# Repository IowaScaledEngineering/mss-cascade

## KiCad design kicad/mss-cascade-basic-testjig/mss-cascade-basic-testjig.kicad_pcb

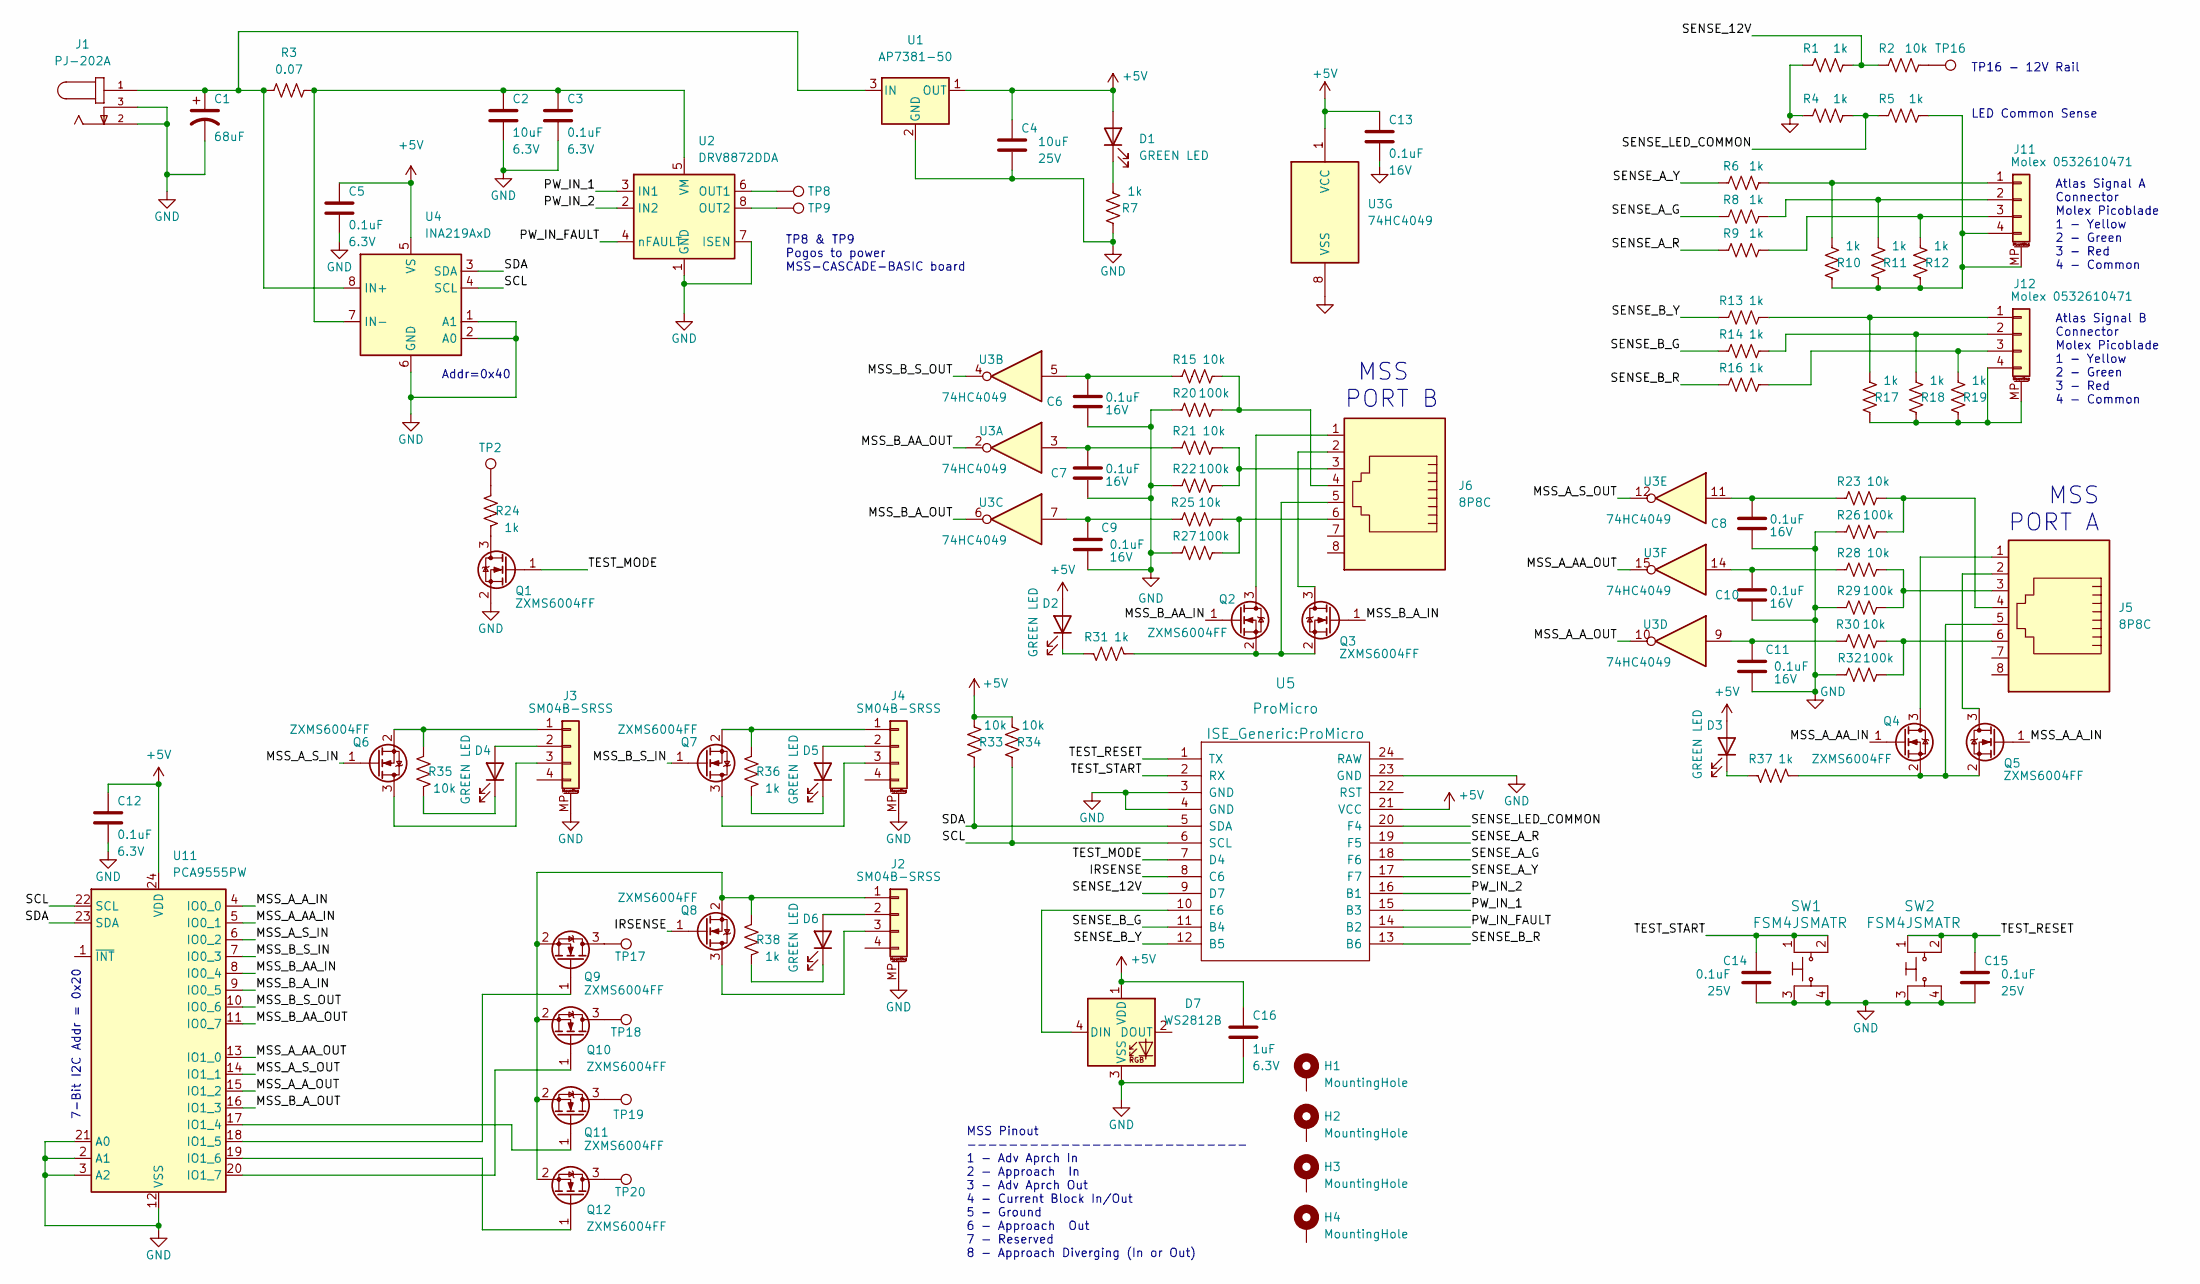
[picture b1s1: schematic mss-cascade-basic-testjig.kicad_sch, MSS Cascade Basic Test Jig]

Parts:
C1: 68uF; CP_Elec_6.3x5.8
C2: 10uF; C_0805_2012Metric; Voltage 6.3V
C3, C5, C12: 0.1uF; C_0805_2012Metric; Voltage 6.3V
C4: 10uF; C_0805_2012Metric; Voltage 25V
C6, C7, C8, C9, C10, C11, C13: 0.1uF; C_0805_2012Metric; Voltage 16V
C14, C15: 0.1uF; C_0805_2012Metric; Voltage 25V
C16: 1uF; C_0805_2012Metric; Voltage 6.3V
D1, D2, D3, D4, D5, D6: GREEN LED; LED_0805_2012Metric
D7: WS2812B; LED_WS2812B_PLCC4_5.0x5.0mm_P3.2mm
H1, H2, H3, H4: MountingHole; MountingHole_3.2mm_M3_Pad
J1: PJ-202A; CUI_PJ-202A
J2, J3, J4: SM04B-SRSS; JST_SH_SM04B-SRSS-TB_1x04-1MP_P1.00mm_Horizontal
J5, J6: 8P8C; RJ45_Amphenol_54602-x08_Horizontal
J11, J12: Molex 0532610471; Molex_PicoBlade_53261-0471_1x04-1MP_P1.25mm_Horizontal
Q1, Q2, Q3, Q4, Q5, Q6, Q7, Q8, Q9, Q10, Q11, Q12: ZXMS6004FF; SOT-23
R1, R4, R5, R6, R7, R8, R9, R10, R11, R12, R13, R14, R16, R17, R18, R19, R24, R31, R36, R37, R38: 1k; R_0805_2012Metric
R2, R15, R21, R23, R25, R28, R30, R33, R34, R35: 10k; R_0805_2012Metric
R3: 0.07; R_2512_6332Metric
R20, R22, R26, R27, R29, R32: 100k; R_0805_2012Metric
SW1, SW2: FSM4JSMATR; TE_FSM4JSMA; MPN FSM4JSMATR; Digi-Key_PN 450-1759-1-ND
TP2, TP8, TP9, TP16, TP17, TP18, TP19, TP20: TestPoint; PinHeader_1x01_P2.54mm_Vertical
U1: AP7381-50; SOT-89-3
U2: DRV8872DDA; Texas_HSOP-8-1EP_3.9x4.9mm_P1.27mm
U3: 74HC4049; SO-16_3.9x9.9mm_P1.27mm
U4: INA219AxD; SOIC-8_3.9x4.9mm_P1.27mm
U5: ProMicro
U11: PCA9555PW; TSSOP-24_4.4x7.8mm_P0.65mm

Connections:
+5V: C4.1, C5.1, C12.1, C13.1, C16.1, D1.2 (A), D2.2 (A), D3.2 (A), D7.1 (VDD), R33.1, R34.1, U1.1 (OUT), U3.1 (VCC), U4.5 (VS), U5.21 (VCC), U11.24 (VDD)
/IRSENSE: Q8.1 (G), U5.8 (C6)
/MSS_A_AA_IN: Q4.1 (G), U11.5 (IO0_1)
/MSS_A_AA_OUT: U3.15, U11.13 (IO1_0)
/MSS_A_A_IN: Q5.1 (G), U11.4 (IO0_0)
/MSS_A_A_OUT: U3.10, U11.15 (IO1_2)
/MSS_A_S_IN: Q6.1 (G), U11.6 (IO0_2)
/MSS_A_S_OUT: U3.12, U11.14 (IO1_1)
/MSS_B_AA_IN: Q2.1 (G), U11.8 (IO0_4)
/MSS_B_AA_OUT: U3.2, U11.11 (IO0_7)
/MSS_B_A_IN: Q3.1 (G), U11.9 (IO0_5)
/MSS_B_A_OUT: U3.6, U11.16 (IO1_3)
/MSS_B_S_IN: Q7.1 (G), U11.7 (IO0_3)
/MSS_B_S_OUT: U3.4, U11.10 (IO0_6)
/PW_IN_1: U2.3 (IN1), U5.15 (B3)
/PW_IN_2: U2.2 (IN2), U5.16 (B1)
/PW_IN_FAULT: U2.4 (nFAULT), U5.14 (B2)
/SCL: R34.2, U4.4 (SCL), U5.6 (SCL), U11.22 (SCL)
/SDA: R33.2, U4.3 (SDA), U5.5 (SDA), U11.23 (SDA)
/SENSE_12V: R1.2, R2.1, U5.9 (D7)
/SENSE_A_G: R8.1, U5.18 (F6)
/SENSE_A_R: R9.1, U5.19 (F5)
/SENSE_A_Y: R6.1, U5.17 (F7)
/SENSE_B_G: R14.1, U5.11 (B4)
/SENSE_B_R: R16.1, U5.13 (B6)
/SENSE_B_Y: R13.1, U5.12 (B5)
/SENSE_LED_COMMON: R4.2, R5.1, U5.20 (F4)
/TEST_MODE: Q1.1 (G), U5.7 (D4)
/TEST_RESET: C15.1, SW2.1, SW2.2, U5.1 (TX)
/TEST_START: C14.1, SW1.1, SW1.2, U5.2 (RX)
GND: C1.2, C2.2, C3.2, C4.2, C5.2, C6.2, C7.2, C8.2, C9.2, C10.2, C11.2, C12.2, C13.2, C14.2, C15.2, C16.2, D7.3 (VSS), J1.2, J1.3, J2.MP (MountPin), J3.MP (MountPin), J4.MP (MountPin), Q1.2 (S), R1.1, R4.1, R7.2, R20.2, R22.2, R26.2, R27.2, R29.2, R32.2, SW1.3, SW1.4, SW2.3, SW2.4, U1.2 (GND), U2.1 (GND), U2.7 (ISEN), U2.9 (GND), U3.8 (VSS), U4.1 (A1), U4.2 (A0), U4.6 (GND), U5.3 (GND), U5.4 (GND), U5.23 (GND), U11.2 (A1), U11.3 (A2), U11.12 (VSS), U11.21 (A0)
unnamed: C1.1, J1.1, R3.2, U1.3 (IN), U4.8 (IN+)
unnamed: C2.1, C3.1, R3.1, U2.5 (VM), U4.7 (IN-)
unnamed: C6.1, R15.2, U3.5
unnamed: C7.1, R21.2, U3.3
unnamed: C8.1, R23.2, U3.11
unnamed: C9.1, R25.2, U3.7
unnamed: C10.1, R28.2, U3.14
unnamed: C11.1, R30.2, U3.9
unnamed: D1.1 (K), R7.1
unnamed: D2.1 (K), R31.2
unnamed: D3.1 (K), R37.2
unnamed: D4.1 (K), R35.1
unnamed: D4.2 (A), J3.2
unnamed: D5.1 (K), R36.1
unnamed: D5.2 (A), J4.2
unnamed: D6.1 (K), R38.1
unnamed: D6.2 (A), J2.2
unnamed: D7.4 (DIN), U5.10 (E6)
unnamed: J2.1, Q8.2 (S), Q9.2 (S), Q10.2 (S), Q11.2 (S), Q12.2 (S), R38.2
unnamed: J2.3, Q8.3 (D)
unnamed: J3.1, Q6.2 (S), R35.2
unnamed: J3.3, Q6.3 (D)
unnamed: J4.1, Q7.2 (S), R36.2
unnamed: J4.3, Q7.3 (D)
unnamed: J5.1, Q4.3 (D)
unnamed: J5.2, Q5.3 (D)
unnamed: J5.3, R28.1, R29.1
unnamed: J5.4, R23.1, R26.1
unnamed: J5.5, Q4.2 (S), Q5.2 (S), R37.1
unnamed: J5.6, R30.1, R32.1
unnamed: J6.1, Q2.3 (D)
unnamed: J6.2, Q3.3 (D)
unnamed: J6.3, R21.1, R22.1
unnamed: J6.4, R15.1, R20.1
unnamed: J6.5, Q2.2 (S), Q3.2 (S), R31.1
unnamed: J6.6, R25.1, R27.1
unnamed: J11.1, R6.2, R10.1
unnamed: J11.2, R8.2, R11.1
unnamed: J11.3, R9.2, R12.1
unnamed: J11.4, J11.MP (MountPin), R5.2, R10.2, R11.2, R12.2
unnamed: J12.1, R13.2, R17.1
unnamed: J12.2, R14.2, R18.1
unnamed: J12.3, R16.2, R19.1
unnamed: J12.4, J12.MP (MountPin), R17.2, R18.2, R19.2
unnamed: Q1.3 (D), R24.1
unnamed: Q9.1 (G), U11.18 (IO1_5)
unnamed: Q9.3 (D), TP17.1
unnamed: Q10.1 (G), U11.20 (IO1_7)
unnamed: Q10.3 (D), TP18.1
unnamed: Q11.1 (G), U11.17 (IO1_4)
unnamed: Q11.3 (D), TP19.1
unnamed: Q12.1 (G), U11.19 (IO1_6)
unnamed: Q12.3 (D), TP20.1
unnamed: R2.2, TP16.1
unnamed: R24.2, TP2.1
unnamed: TP8.1, U2.6 (OUT1)
unnamed: TP9.1, U2.8 (OUT2)

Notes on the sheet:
MSS PORT A
Addr=0x40
Atlas Signal B Connector Molex Picoblade 1 - Yellow 2 - Green 3 - Red 4 - Common
MSS PORT B
MSS Pinout --------------------------- 1 - Adv Aprch In 2 - Approach In 3 - Adv Aprch Out 4 - Current Block In/Out 5 - Ground 6 - Approach Out 7 - Reserved 8 - Approach Diverging (In or Out)
TP8 & TP9 Pogos to power MSS-CASCADE-BASIC board
Atlas Signal A Connector Molex Picoblade 1 - Yellow 2 - Green 3 - Red 4 - Common
TP16 - 12V Rail
LED Common Sense
7-Bit I2C Addr = 0x20

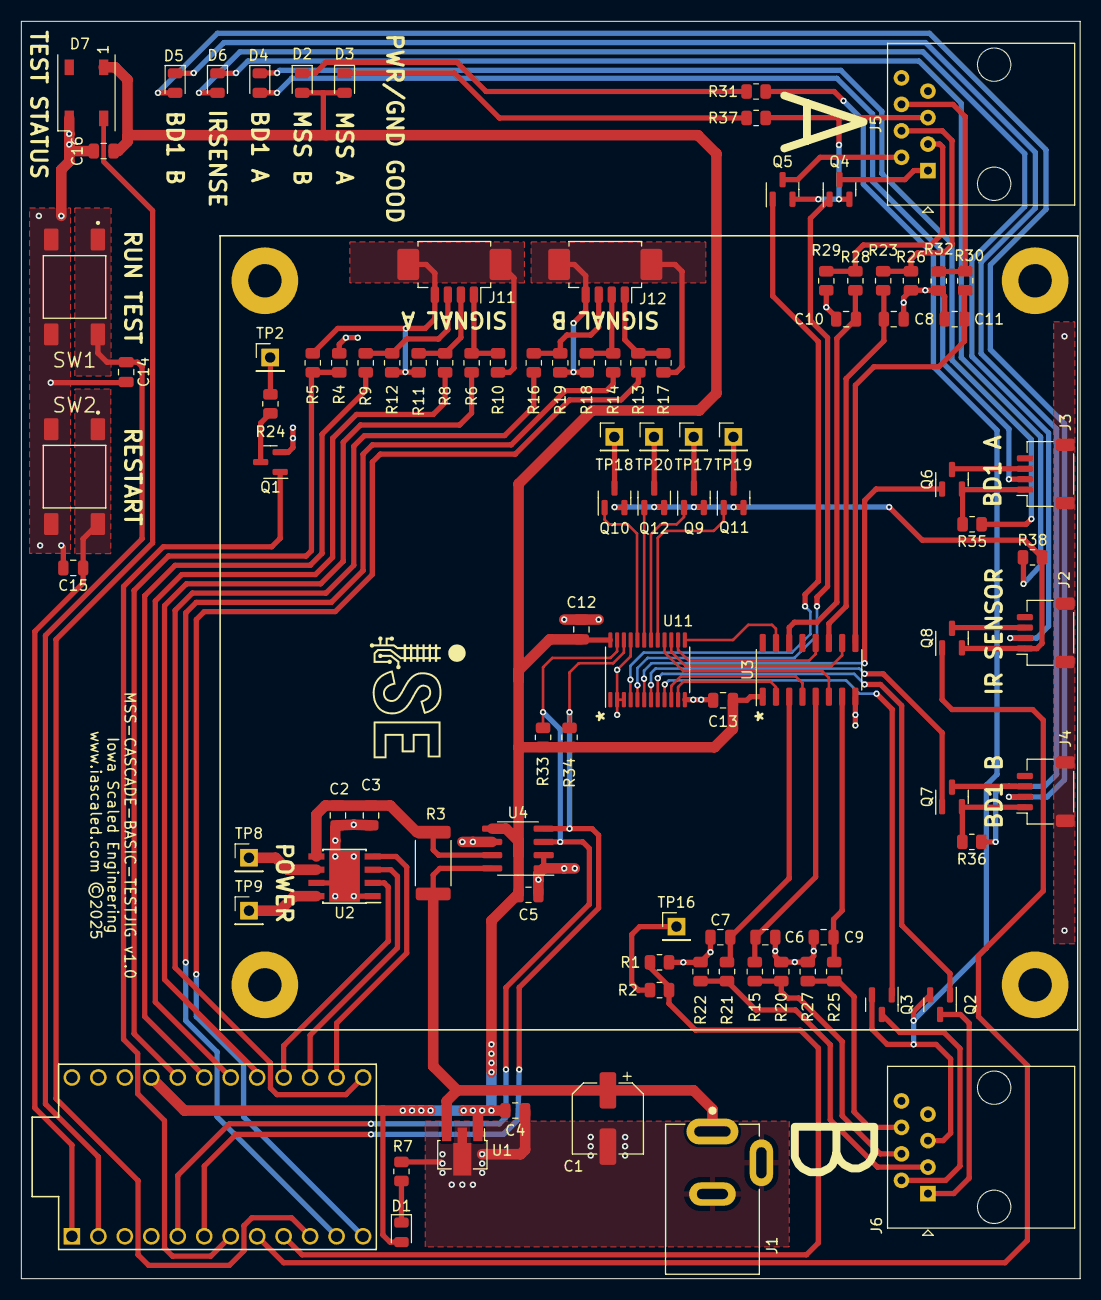
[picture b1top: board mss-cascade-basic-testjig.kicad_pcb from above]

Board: 2 copper layers, 101.6 x 120.7 mm, 101 parts (0 on the bottom side), 88 nets.

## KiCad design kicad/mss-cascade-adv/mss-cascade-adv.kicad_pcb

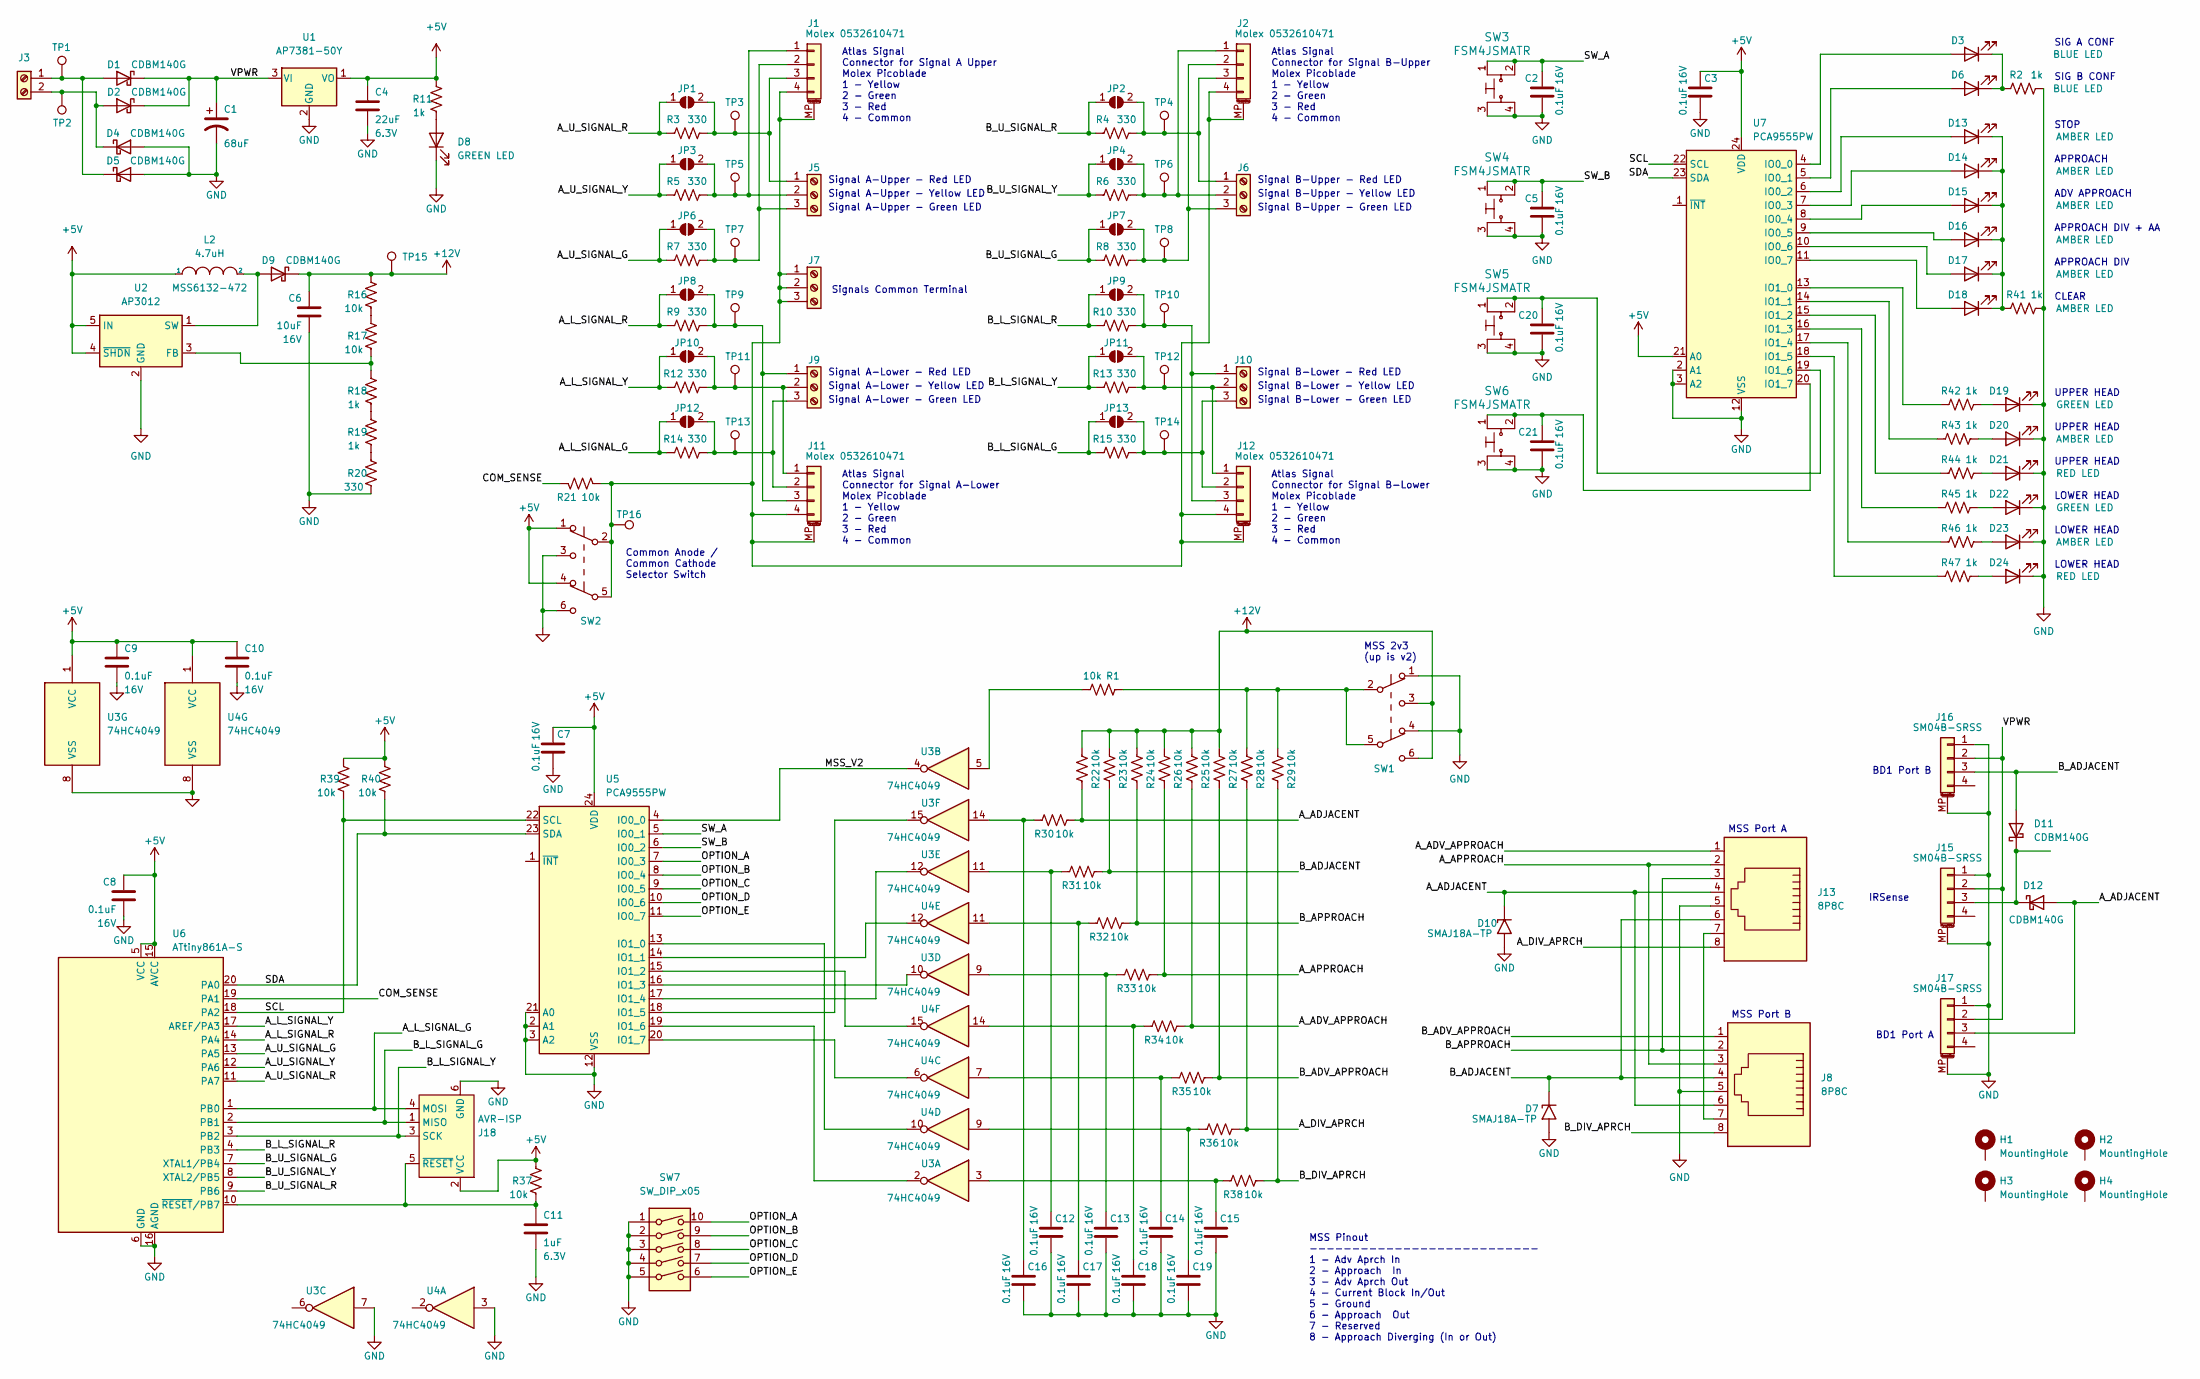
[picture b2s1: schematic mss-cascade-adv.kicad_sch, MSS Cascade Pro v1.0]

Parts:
C1: 68uF; CP_Elec_6.3x5.8
C2, C3, C5, C7, C8, C9, C10, C12, C13, C14, C15, C16, C17, C18, C19, C20, C21: 0.1uF; C_0805_2012Metric; Voltage 16V
C4: 22uF; C_0805_2012Metric; Voltage 6.3V
C6: 10uF; C_0805_2012Metric; Voltage 16V
C11: 1uF; C_0805_2012Metric; Voltage 6.3V
D1, D2, D4, D5, D9, D11, D12: CDBM140G; SOD-123T
D3, D6: BLUE LED; LED_0805_2012Metric
D7, D10: SMAJ18A-TP; D_SMA
D8, D19, D22: GREEN LED; LED_0805_2012Metric
D13, D14, D15, D16, D17, D18, D20, D23: AMBER LED; LED_0805_2012Metric
D21, D24: RED LED; LED_0805_2012Metric
H1, H2, H3, H4: MountingHole; MountingHole_3.2mm_M3_Pad
J1, J2, J11, J12: Molex 0532610471; Molex_PicoBlade_53261-0471_1x04-1MP_P1.25mm_Horizontal
J3: Screw_Terminal_01x02; TerminalBlock_RND_205-00012_1x02_P5.00mm_Horizontal
J5, J6, J7, J9, J10: Screw_Terminal_01x02; TerminalBlock_MetzConnect_Type059_RT06303HBWC_1x03_P3.50mm_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
J8, J13: 8P8C; RJ45_Amphenol_54602-x08_Horizontal
J15, J16, J17: SM04B-SRSS; JST_SH_SM04B-SRSS-TB_1x04-1MP_P1.00mm_Horizontal
J18: AVR-ISP; Tag-Connect_TC2030-IDC-NL_2x03_P1.27mm_Vertical
JP1, JP2, JP3, JP4, JP6, JP7, JP8, JP9, JP10, JP11, JP12, JP13: SolderJumper_2_Open; SolderJumper-2_P1.3mm_Open_RoundedPad1.0x1.5mm
L2: 4.7uH; MSS6132-xxxMLC
R1, R16, R17, R21, R22, R23, R24, R25, R26, R27, R28, R29, R30, R31, R32, R33, R34, R35, R36, R37, R38, R39, R40: 10k; R_0805_2012Metric
R2, R11, R18, R19, R41, R42, R43, R44, R45, R46, R47: 1k; R_0805_2012Metric
R3, R4, R5, R6, R7, R8, R9, R10, R12, R13, R14, R15, R20: 330; R_0805_2012Metric
SW1, SW2: JS202011SCQN; SW_JS202011SCQN
SW3, SW4, SW5, SW6: FSM4JSMATR; TE_FSM4JSMA; MPN FSM4JSMATR; Digi-Key_PN 450-1759-1-ND
SW7: SW_DIP_x05; SW_DIP_SPSTx05_Slide_6.7x14.26mm_W8.61mm_P2.54mm_LowProfile
TP1, TP2, TP3, TP4, TP5, TP6, TP7, TP8, TP9, TP10, TP11, TP12, TP13, TP14, TP15, TP16: TestPoint; TestPoint_Pad_D2.0mm
U1: AP7381-50Y; SOT-89-3
U2: AP3012; SOT-23-5
U3, U4: 74HC4049; SO-16_3.9x9.9mm_P1.27mm
U5, U7: PCA9555PW; TSSOP-24_4.4x7.8mm_P0.65mm
U6: ATtiny861A-S; SOIC-20W_7.5x12.8mm_P1.27mm

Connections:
+5V: C3.1, C4.1, C7.1, C8.1, C9.1, C10.1, J18.2 (VCC), L2.1, R11.2, R37.2, R39.2, R40.2, SW2.1 (A), SW2.4 (A), U1.1 (VO), U2.4 (~SHDN), U2.5 (IN), U3.1 (VCC), U4.1 (VCC), U5.24 (VDD), U6.5 (VCC), U6.15 (AVCC), U7.21 (A0), U7.24 (VDD)
+12V: C6.1, D9.1 (K), R16.2, R22.1, R23.1, R24.1, R25.1, R26.2, R27.1, SW1.3 (C), SW1.6 (C), TP15.1
/A_ADJACENT: D10.1 (A1), D12.2 (A), J8.6, J13.4, J17.3, R22.2, R30.1
/A_ADV_APPROACH: J13.1, R25.2, R34.1
/A_APPROACH: J8.3, J13.2, R26.1, R33.1
/A_DIV_APRCH: J13.8, R28.2, R36.1
/A_L_SIGNAL_G: J18.4 (MOSI), JP12.1 (A), R14.1, U6.1 (PB0)
/A_L_SIGNAL_R: JP8.1 (A), R9.1, U6.14 (PA4)
/A_L_SIGNAL_Y: JP10.1 (A), R12.1, U6.17 (AREF/PA3)
/A_U_SIGNAL_G: JP6.1 (A), R7.1, U6.13 (PA5)
/A_U_SIGNAL_R: JP1.1 (A), R3.1, U6.11 (PA7)
/A_U_SIGNAL_Y: JP3.1 (A), R5.1, U6.12 (PA6)
/B_ADJACENT: D7.1 (A1), D11.2 (A), J8.4, J13.6, J16.3, R23.2, R31.1
/B_ADV_APPROACH: J8.1, R27.2, R35.1
/B_APPROACH: J8.2, J13.3, R24.2, R32.1
/B_DIV_APRCH: J8.8, R29.2, R38.1
/B_L_SIGNAL_G: J18.1 (MISO), JP13.1 (A), R15.1, U6.2 (PB1)
/B_L_SIGNAL_R: JP9.1 (A), R10.1, U6.4 (PB3)
/B_L_SIGNAL_Y: J18.3 (SCK), JP11.1 (A), R13.1, U6.3 (PB2)
/B_U_SIGNAL_G: JP7.1 (A), R8.1, U6.7 (XTAL1/PB4)
/B_U_SIGNAL_R: JP2.1 (A), R4.1, U6.9 (PB6)
/B_U_SIGNAL_Y: JP4.1 (A), R6.1, U6.8 (XTAL2/PB5)
/COM_SENSE: R21.1, U6.19 (PA1)
/MSS_V2: U3.4, U5.4 (IO0_0)
/OPTION_A: SW7.10, U5.7 (IO0_3)
/OPTION_B: SW7.9, U5.8 (IO0_4)
/OPTION_C: SW7.8, U5.9 (IO0_5)
/OPTION_D: SW7.7, U5.10 (IO0_6)
/OPTION_E: SW7.6, U5.11 (IO0_7)
/SCL: R39.1, U5.22 (SCL), U6.18 (PA2), U7.22 (SCL)
/SDA: R40.1, U5.23 (SDA), U6.20 (PA0), U7.23 (SDA)
/SW_A: C2.1, SW3.1, SW3.2, U5.5 (IO0_1)
/SW_B: C5.1, SW4.1, SW4.2, U5.6 (IO0_2)
/VPWR: C1.1, D1.1 (K), D2.1 (K), J15.2, J16.2, J17.2, U1.3 (VI)
GND: C1.2, C2.2, C3.2, C4.2, C5.2, C6.2, C7.2, C8.2, C9.2, C10.2, C11.2, C12.2, C13.2, C14.2, C15.2, C16.2, C17.2, C18.2, C19.2, C20.2, C21.2, D4.2 (A), D5.2 (A), D7.2 (A2), D8.1 (K), D10.2 (A2), D19.1 (K), D20.1 (K), D21.1 (K), D22.1 (K), D23.1 (K), D24.1 (K), J8.5, J13.5, J15.1, J15.MP (MountPin), J16.1, J16.MP (MountPin), J17.1, J17.MP (MountPin), J18.6 (GND), R2.2, R20.1, R41.2, SW1.1 (A), SW1.4 (A), SW2.3 (C), SW2.6 (C), SW3.3, SW3.4, SW4.3, SW4.4, SW5.3, SW5.4, SW6.3, SW6.4, SW7.1, SW7.2, SW7.3, SW7.4, SW7.5, U1.2 (GND), U2.2 (GND), U3.7, U3.8 (VSS), U4.3, U4.8 (VSS), U5.2 (A1), U5.3 (A2), U5.12 (VSS), U5.21 (A0), U6.6 (GND), U6.16 (AGND), U7.2 (A1), U7.3 (A2), U7.12 (VSS)
unnamed: C11.1, J18.5 (~RESET), R37.1, U6.10 (~RESET/PB7)
unnamed: C12.1, R31.2, U3.11
unnamed: C13.1, R33.2, U3.9
unnamed: C14.1, R35.2, U4.7
unnamed: C15.1, R38.2, U3.3
unnamed: C16.1, R30.2, U3.14
unnamed: C17.1, R32.2, U4.11
unnamed: C18.1, R34.2, U4.14
unnamed: C19.1, R36.2, U4.9
unnamed: C20.1, SW5.1, SW5.2, U7.19 (IO1_6)
unnamed: C21.1, SW6.1, SW6.2, U7.20 (IO1_7)
unnamed: D1.2 (A), D5.1 (K), J3.1, TP1.1
unnamed: D2.2 (A), D4.1 (K), J3.2, TP2.1
unnamed: D3.1 (K), D6.1 (K), R2.1
unnamed: D3.2 (A), U7.4 (IO0_0)
unnamed: D6.2 (A), U7.5 (IO0_1)
unnamed: D8.2 (A), R11.1
unnamed: D9.2 (A), L2.2, U2.1 (SW)
unnamed: D11.1 (K), D12.1 (K), J15.3
unnamed: D13.1 (K), D14.1 (K), D15.1 (K), D16.1 (K), D17.1 (K), D18.1 (K), R41.1
unnamed: D13.2 (A), U7.6 (IO0_2)
unnamed: D14.2 (A), U7.7 (IO0_3)
unnamed: D15.2 (A), U7.8 (IO0_4)
unnamed: D16.2 (A), U7.9 (IO0_5)
unnamed: D17.2 (A), U7.10 (IO0_6)
unnamed: D18.2 (A), U7.11 (IO0_7)
unnamed: D19.2 (A), R42.2
unnamed: D20.2 (A), R43.2
unnamed: D21.2 (A), R44.2
unnamed: D22.2 (A), R45.2
unnamed: D23.2 (A), R46.2
unnamed: D24.2 (A), R47.2
unnamed: J1.1, J5.2, JP3.2 (B), R5.2, TP5.1
unnamed: J1.2, J5.3, JP6.2 (B), R7.2, TP7.1
unnamed: J1.3, J5.1, JP1.2 (B), R3.2, TP3.1
unnamed: J1.4, J1.MP (MountPin), J2.4, J2.MP (MountPin), J7.1, J7.2, J7.3, J11.4, J11.MP (MountPin), J12.4, J12.MP (MountPin), R21.2, SW2.2 (B), SW2.5 (B), TP16.1
unnamed: J2.1, J6.2, JP4.2 (B), R6.2, TP6.1
unnamed: J2.2, J6.3, JP7.2 (B), R8.2, TP8.1
unnamed: J2.3, J6.1, JP2.2 (B), R4.2, TP4.1
unnamed: J10.1, J12.3, JP9.2 (B), R10.2, TP10.1
unnamed: J10.2, J12.1, JP11.2 (B), R13.2, TP12.1
unnamed: J10.3, J12.2, JP13.2 (B), R15.2, TP14.1
unnamed: J9.2, J11.1, JP10.2 (B), R12.2, TP11.1
unnamed: J9.3, J11.2, JP12.2 (B), R14.2, TP13.1
unnamed: J9.1, J11.3, JP8.2 (B), R9.2, TP9.1
unnamed: J8.7, J13.7
unnamed: R1.1, U3.5
unnamed: R1.2, R28.1, R29.1, SW1.2 (B), SW1.5 (B)
unnamed: R16.1, R17.2
unnamed: R17.1, R18.2, U2.3 (FB)
unnamed: R18.1, R19.2
unnamed: R19.1, R20.2
unnamed: R42.1, U7.13 (IO1_0)
unnamed: R43.1, U7.14 (IO1_1)
unnamed: R44.1, U7.15 (IO1_2)
unnamed: R45.1, U7.16 (IO1_3)
unnamed: R46.1, U7.17 (IO1_4)
unnamed: R47.1, U7.18 (IO1_5)
unnamed: U3.2, U5.19 (IO1_6)
unnamed: U3.10, U5.16 (IO1_3)
unnamed: U3.12, U5.17 (IO1_4)
unnamed: U3.15, U5.18 (IO1_5)
unnamed: U4.6, U5.20 (IO1_7)
unnamed: U4.10, U5.13 (IO1_0)
unnamed: U4.12, U5.14 (IO1_1)
unnamed: U4.15, U5.15 (IO1_2)

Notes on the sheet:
UPPER HEAD
Signal A-Upper - Yellow LED
APPROACH
Common Anode / Common Cathode Selector Switch
Atlas Signal Connector for Signal A Upper Molex Picoblade 1 - Yellow 2 - Green 3 - Red 4 - Common
LOWER HEAD
Signal A-Lower - Green LED
MSS 2v3 (up is v2)
MSS Port A
IRSense
Signal B-Lower - Red LED
Signal A-Lower - Yellow LED
CLEAR
BD1 Port B
MSS Port B
APPROACH DIV
SIG A CONF
Atlas Signal Connector for Signal B-Upper Molex Picoblade 1 - Yellow 2 - Green 3 - Red 4 - Common
STOP
BD1 Port A
Signals Common Terminal
ADV APPROACH
SIG B CONF
Signal B-Upper - Red LED
APPROACH DIV + AA
Signal A-Lower - Red LED
Signal B-Lower - Green LED
Atlas Signal Connector for Signal B-Lower Molex Picoblade 1 - Yellow 2 - Green 3 - Red 4 - Common
Atlas Signal Connector for Signal A-Lower Molex Picoblade 1 - Yellow 2 - Green 3 - Red 4 - Common
Signal A-Upper - Green LED
Signal B-Upper - Green LED
Signal B-Lower - Yellow LED
Signal B-Upper - Yellow LED
Signal A-Upper - Red LED
MSS Pinout --------------------------- 1 - Adv Aprch In 2 - Approach In 3 - Adv Aprch Out 4 - Current Block In/Out 5 - Ground 6 - Approach Out 7 - Reserved 8 - Approach Diverging (In or Out)

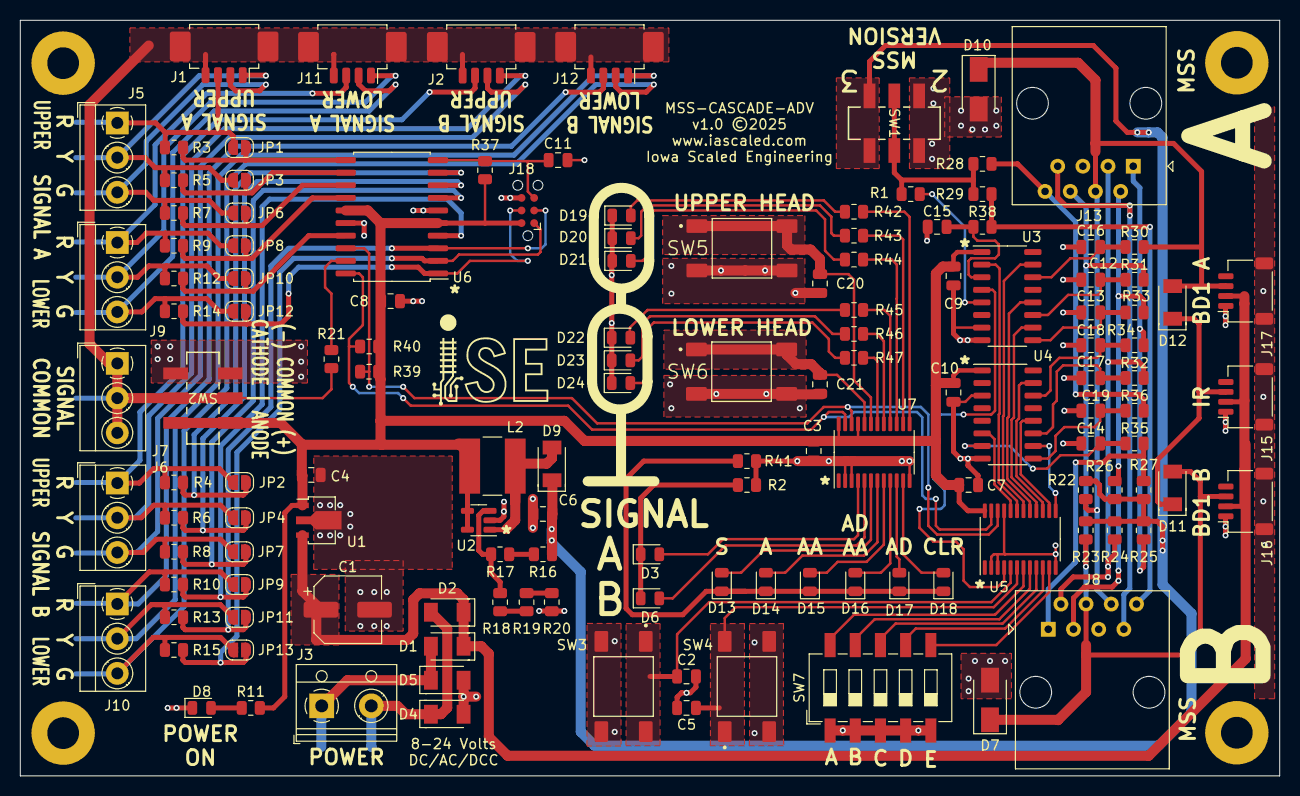
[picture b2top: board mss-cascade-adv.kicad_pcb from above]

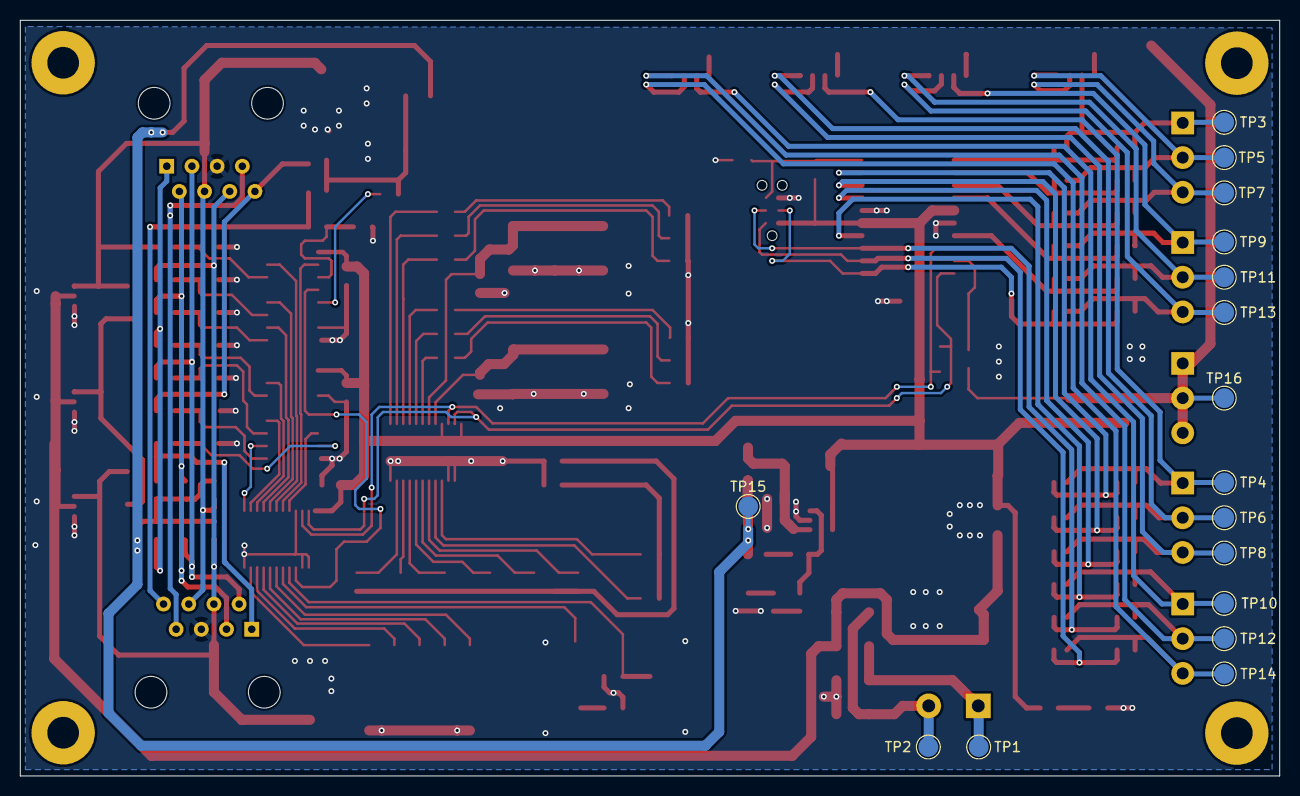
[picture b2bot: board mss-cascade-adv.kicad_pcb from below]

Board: 2 copper layers, 127.0 x 76.2 mm, 155 parts (16 on the bottom side), 101 nets.

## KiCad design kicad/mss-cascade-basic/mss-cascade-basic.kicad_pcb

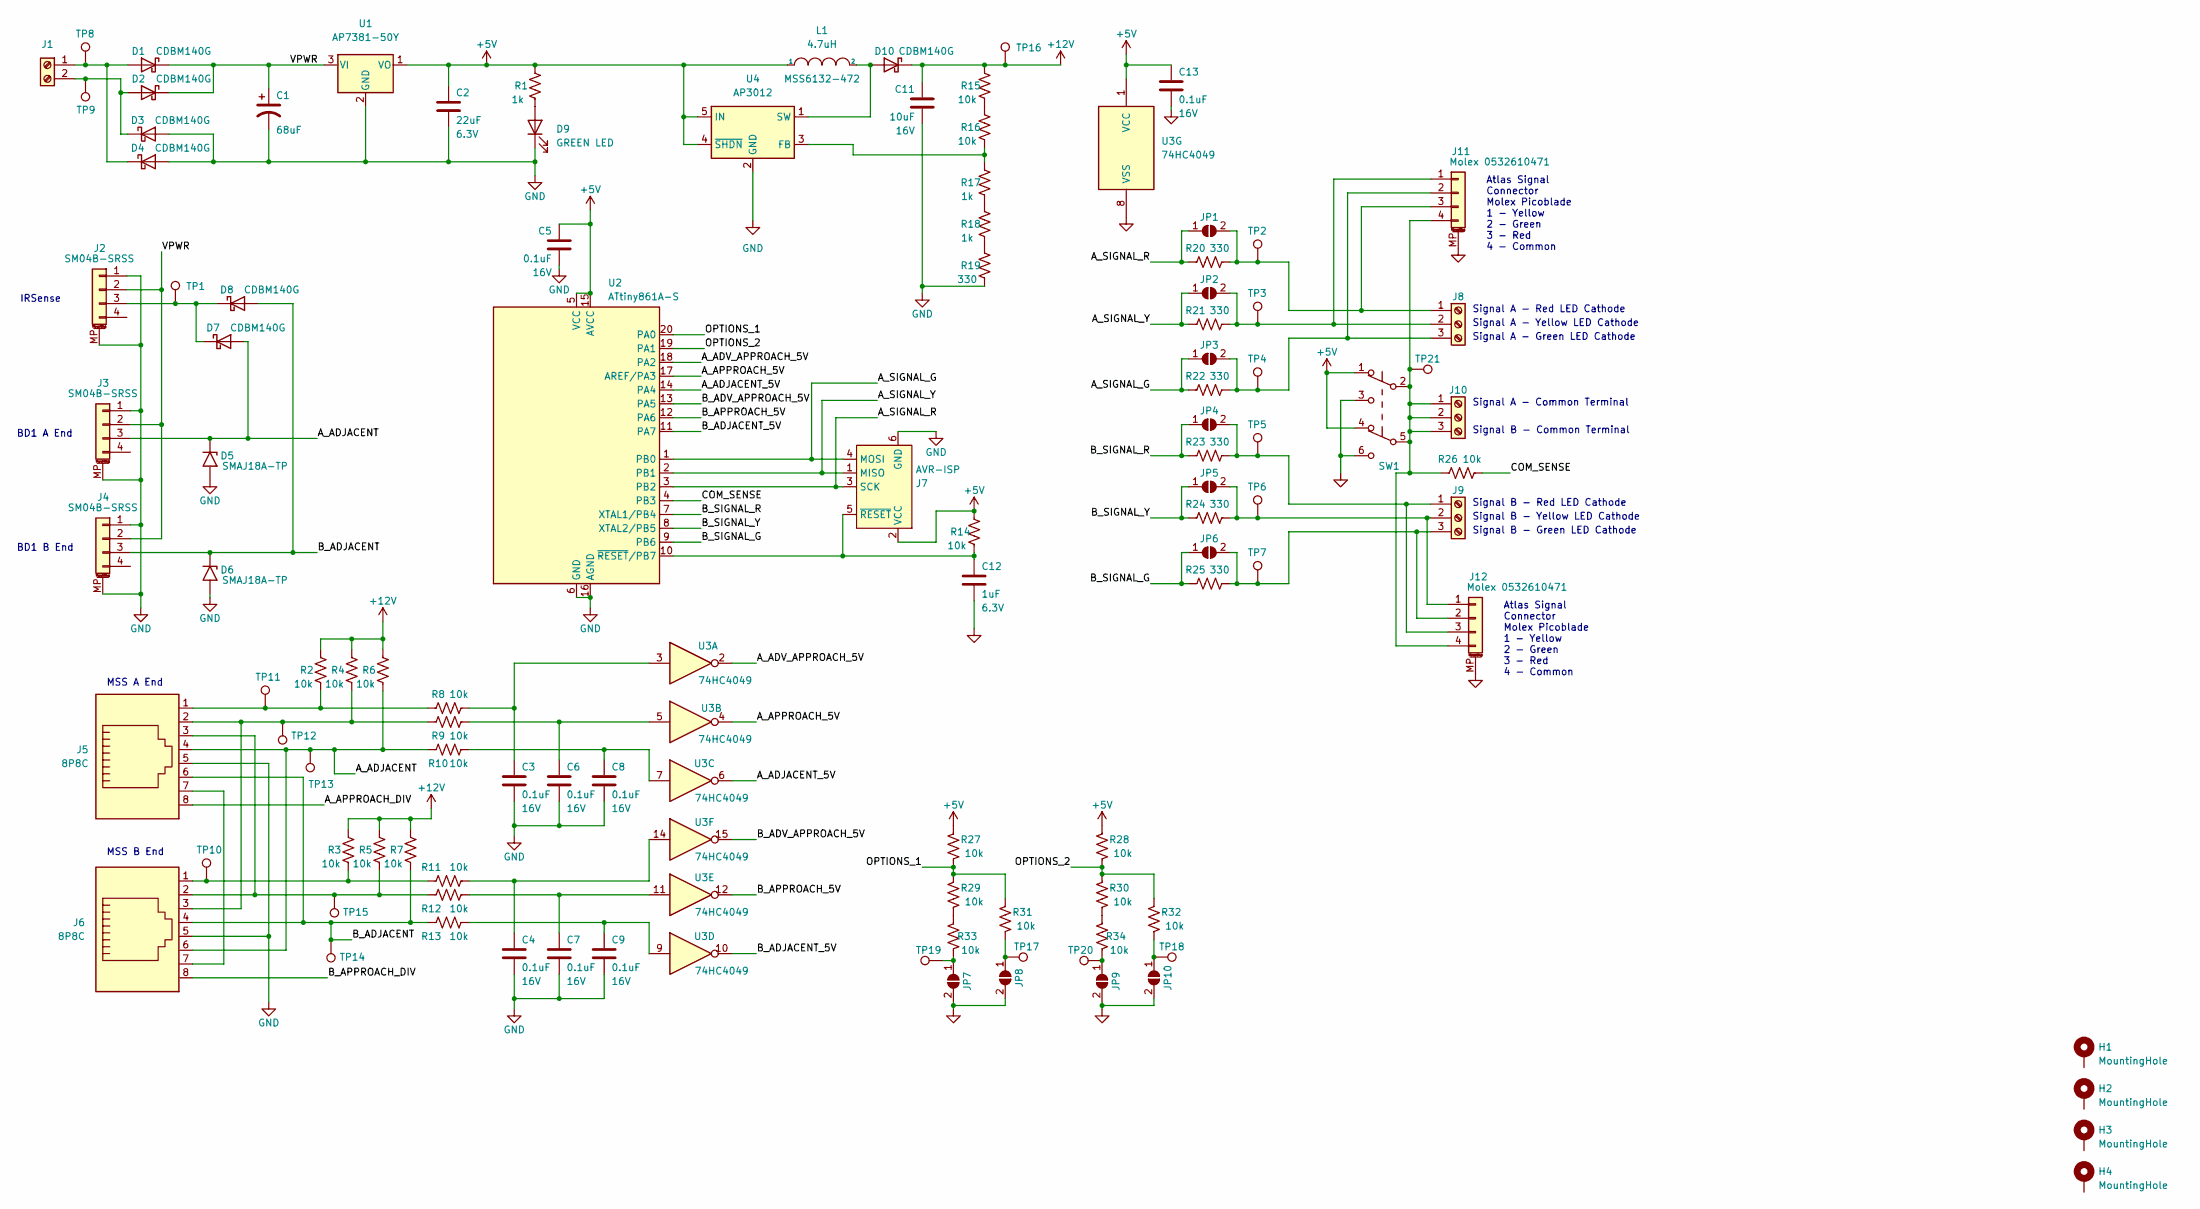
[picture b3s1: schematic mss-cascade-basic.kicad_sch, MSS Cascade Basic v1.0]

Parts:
C1: 68uF; CP_Elec_6.3x5.8
C2: 22uF; C_0805_2012Metric; Voltage 6.3V
C3, C4, C5, C6, C7, C8, C9, C13: 0.1uF; C_0805_2012Metric; Voltage 16V
C11: 10uF; C_0805_2012Metric; Voltage 16V
C12: 1uF; C_0805_2012Metric; Voltage 6.3V
D1, D2, D3, D4, D7, D8, D10: CDBM140G; SOD-123T
D5, D6: SMAJ18A-TP; D_SMA
D9: GREEN LED; LED_0805_2012Metric
H1, H2, H3, H4: MountingHole; MountingHole_3.2mm_M3_Pad
J1: Screw_Terminal_01x02; TerminalBlock_RND_205-00012_1x02_P5.00mm_Horizontal
J2, J3, J4: SM04B-SRSS; JST_SH_SM04B-SRSS-TB_1x04-1MP_P1.00mm_Horizontal
J5, J6: 8P8C; RJ45_Amphenol_54602-x08_Horizontal
J7: AVR-ISP; Tag-Connect_TC2030-IDC-NL_2x03_P1.27mm_Vertical
J8, J9, J10: Screw_Terminal_01x02; TerminalBlock_MetzConnect_Type059_RT06303HBWC_1x03_P3.50mm_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
J11, J12: Molex 0532610471; Molex_PicoBlade_53261-0471_1x04-1MP_P1.25mm_Horizontal
JP1, JP2, JP3, JP4, JP5, JP6, JP7, JP8, JP9, JP10: SolderJumper_2_Open; SolderJumper-2_P1.3mm_Open_RoundedPad1.0x1.5mm
L1: 4.7uH; MSS6132-xxxMLC
R1, R17, R18: 1k; R_0805_2012Metric
R2, R3, R4, R5, R6, R7, R8, R9, R10, R11, R12, R13, R14, R15, R16, R26, R27, R28, R29, R30, R31, R32, R33, R34: 10k; R_0805_2012Metric
R19, R20, R21, R22, R23, R24, R25: 330; R_0805_2012Metric
SW1: JS202011SCQN; SW_JS202011SCQN
TP1, TP2, TP3, TP4, TP5, TP6, TP7, TP8, TP9, TP10, TP11, TP12, TP13, TP14, TP15, TP16, TP17, TP18, TP19, TP20, TP21: TestPoint; TestPoint_Pad_D2.0mm
U1: AP7381-50Y; SOT-89-3
U2: ATtiny861A-S; SOIC-20W_7.5x12.8mm_P1.27mm
U3: 74HC4049; SO-16_3.9x9.9mm_P1.27mm
U4: AP3012; SOT-23-5

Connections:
+5V: C2.1, C5.1, C13.1, J7.2 (VCC), L1.1, R1.2, R14.2, R27.2, R28.2, SW1.1 (A), SW1.4 (A), U1.1 (VO), U2.5 (VCC), U2.15 (AVCC), U3.1 (VCC), U4.4 (~SHDN), U4.5 (IN)
+12V: C11.1, D10.1 (K), R2.2, R3.2, R4.2, R5.2, R6.2, R7.2, R15.2, TP16.1
/A_ADJACENT: D5.1 (A1), D7.2 (A), J3.3, J5.4, J6.6, R6.1, R10.2, TP13.1
/A_ADJACENT_5V: U2.14 (PA4), U3.6
/A_ADV_APPROACH_5V: U2.18 (PA2), U3.2
/A_APPROACH_5V: U2.17 (AREF/PA3), U3.4
/A_APPROACH_DIV: J5.8
/A_SIGNAL_G: J7.4 (MOSI), JP3.1 (A), R22.1, U2.1 (PB0)
/A_SIGNAL_R: J7.3 (SCK), JP1.1 (A), R20.1, U2.3 (PB2)
/A_SIGNAL_Y: J7.1 (MISO), JP2.1 (A), R21.1, U2.2 (PB1)
/B_ADJACENT: D6.1 (A1), D8.2 (A), J4.3, J5.6, J6.4, R7.1, R13.2, TP14.1
/B_ADJACENT_5V: U2.11 (PA7), U3.10
/B_ADV_APPROACH_5V: U2.13 (PA5), U3.15
/B_APPROACH_5V: U2.12 (PA6), U3.12
/B_APPROACH_DIV: J6.8
/B_SIGNAL_G: JP6.1 (A), R25.1, U2.9 (PB6)
/B_SIGNAL_R: JP4.1 (A), R23.1, U2.7 (XTAL1/PB4)
/B_SIGNAL_Y: JP5.1 (A), R24.1, U2.8 (XTAL2/PB5)
/COM_SENSE: R26.2, U2.4 (PB3)
/OPTIONS_1: R27.1, R29.2, R31.2, U2.20 (PA0)
/OPTIONS_2: R28.1, R30.2, R32.2, U2.19 (PA1)
/VPWR: C1.1, D1.1 (K), D2.1 (K), J2.2, J3.2, J4.2, U1.3 (VI)
GND: C1.2, C2.2, C3.2, C4.2, C5.2, C6.2, C7.2, C8.2, C9.2, C11.2, C12.2, C13.2, D3.2 (A), D4.2 (A), D5.2 (A2), D6.2 (A2), D9.1 (K), J2.1, J2.MP (MountPin), J3.1, J3.MP (MountPin), J4.1, J4.MP (MountPin), J5.5, J6.5, J7.6 (GND), J11.MP (MountPin), J12.MP (MountPin), JP7.2 (B), JP8.2 (B), JP9.2 (B), JP10.2 (B), R19.1, SW1.3 (C), SW1.6 (C), U1.2 (GND), U2.6 (GND), U2.16 (AGND), U3.8 (VSS), U4.2 (GND)
unnamed: C3.1, R8.1, U3.3
unnamed: C4.1, R11.1, U3.14
unnamed: C6.1, R9.1, U3.5
unnamed: C7.1, R12.1, U3.11
unnamed: C8.1, R10.1, U3.7
unnamed: C9.1, R13.1, U3.9
unnamed: C12.1, J7.5 (~RESET), R14.1, U2.10 (~RESET/PB7)
unnamed: D1.2 (A), D4.1 (K), J1.1, TP8.1
unnamed: D2.2 (A), D3.1 (K), J1.2, TP9.1
unnamed: D7.1 (K), D8.1 (K), J2.3, TP1.1
unnamed: D9.2 (A), R1.1
unnamed: D10.2 (A), L1.2, U4.1 (SW)
unnamed: J5.1, R2.1, R8.2, TP11.1
unnamed: J5.2, J6.3, R4.1, R9.2, TP12.1
unnamed: J5.3, J6.2, R5.1, R12.2, TP15.1
unnamed: J5.7, J6.7
unnamed: J6.1, R3.1, R11.2, TP10.1
unnamed: J10.1, J10.2, J10.3, J11.4, J12.4, R26.1, SW1.2 (B), SW1.5 (B), TP21.1
unnamed: J8.2, J11.1, JP2.2 (B), R21.2, TP3.1
unnamed: J8.3, J11.2, JP3.2 (B), R22.2, TP4.1
unnamed: J8.1, J11.3, JP1.2 (B), R20.2, TP2.1
unnamed: J9.2, J12.1, JP5.2 (B), R24.2, TP6.1
unnamed: J9.3, J12.2, JP6.2 (B), R25.2, TP7.1
unnamed: J9.1, J12.3, JP4.2 (B), R23.2, TP5.1
unnamed: JP7.1 (A), R33.1, TP19.1
unnamed: JP8.1 (A), R31.1, TP17.1
unnamed: JP9.1 (A), R34.1, TP20.1
unnamed: JP10.1 (A), R32.1, TP18.1
unnamed: R15.1, R16.2
unnamed: R16.1, R17.2, U4.3 (FB)
unnamed: R17.1, R18.2
unnamed: R18.1, R19.2
unnamed: R29.1, R33.2
unnamed: R30.1, R34.2

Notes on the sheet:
IRSense
Signal A - Yellow LED Cathode
Signal A - Red LED Cathode
Signal A - Common Terminal
Atlas Signal Connector Molex Picoblade 1 - Yellow 2 - Green 3 - Red 4 - Common
Signal B - Red LED Cathode
Signal B - Green LED Cathode
MSS B End
Signal B - Common Terminal
Signal B - Yellow LED Cathode
BD1 A End
BD1 B End
Signal A - Green LED Cathode
MSS A End

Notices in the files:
kicad/mss-cascade-adv/mss-cascade-adv.kicad_pcb:
v1.0 ©2025
kicad/mss-cascade-basic-testjig/mss-cascade-basic-testjig.kicad_pcb:
www.iascaled.com ©2025
kicad/mss-cascade-basic/mss-cascade-basic.kicad_pcb:
www.iascaled.com ©2024
